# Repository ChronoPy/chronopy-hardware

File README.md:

# ChronoPy - Open Hardware, hacker freindly, wrist watch based on the OHS2020 badge
* [Hackaday.io project page](https://hackaday.io/project/168483-open-hardware-summit-2020-badge)
* [OHS 2020 website](http://2020.oshwa.org/)

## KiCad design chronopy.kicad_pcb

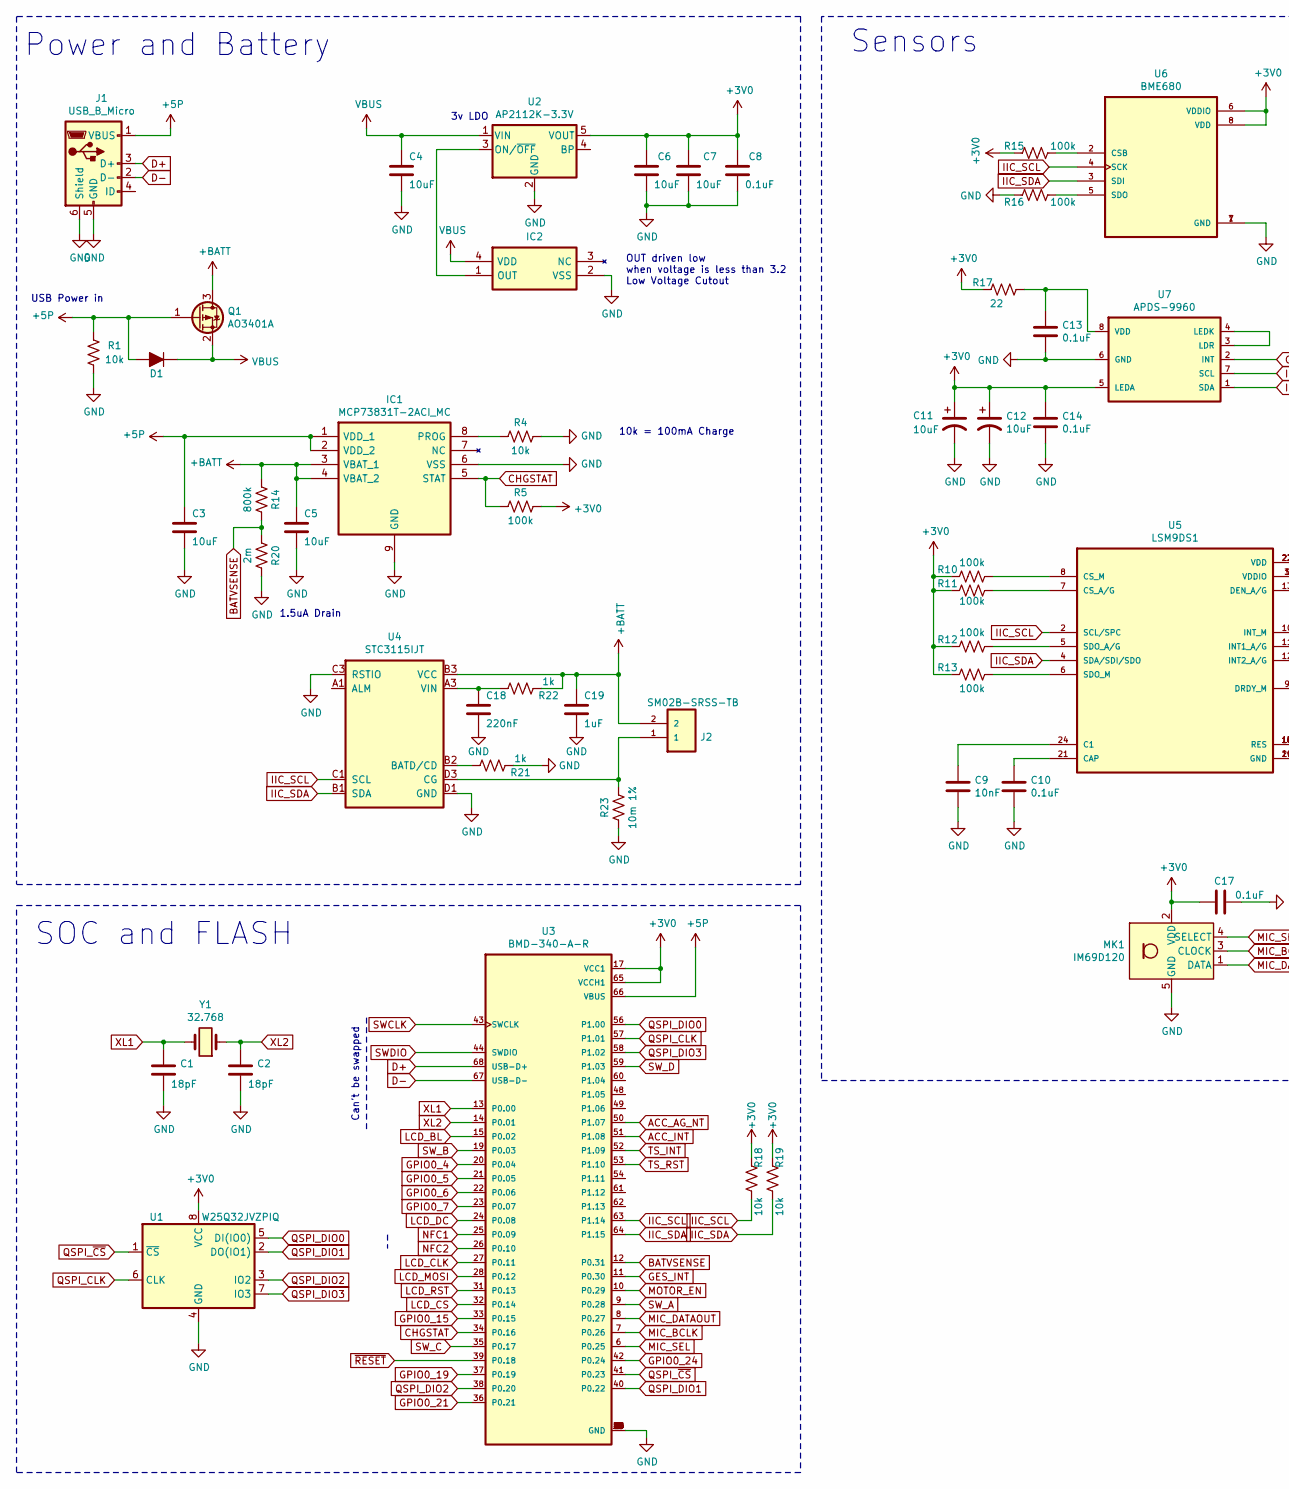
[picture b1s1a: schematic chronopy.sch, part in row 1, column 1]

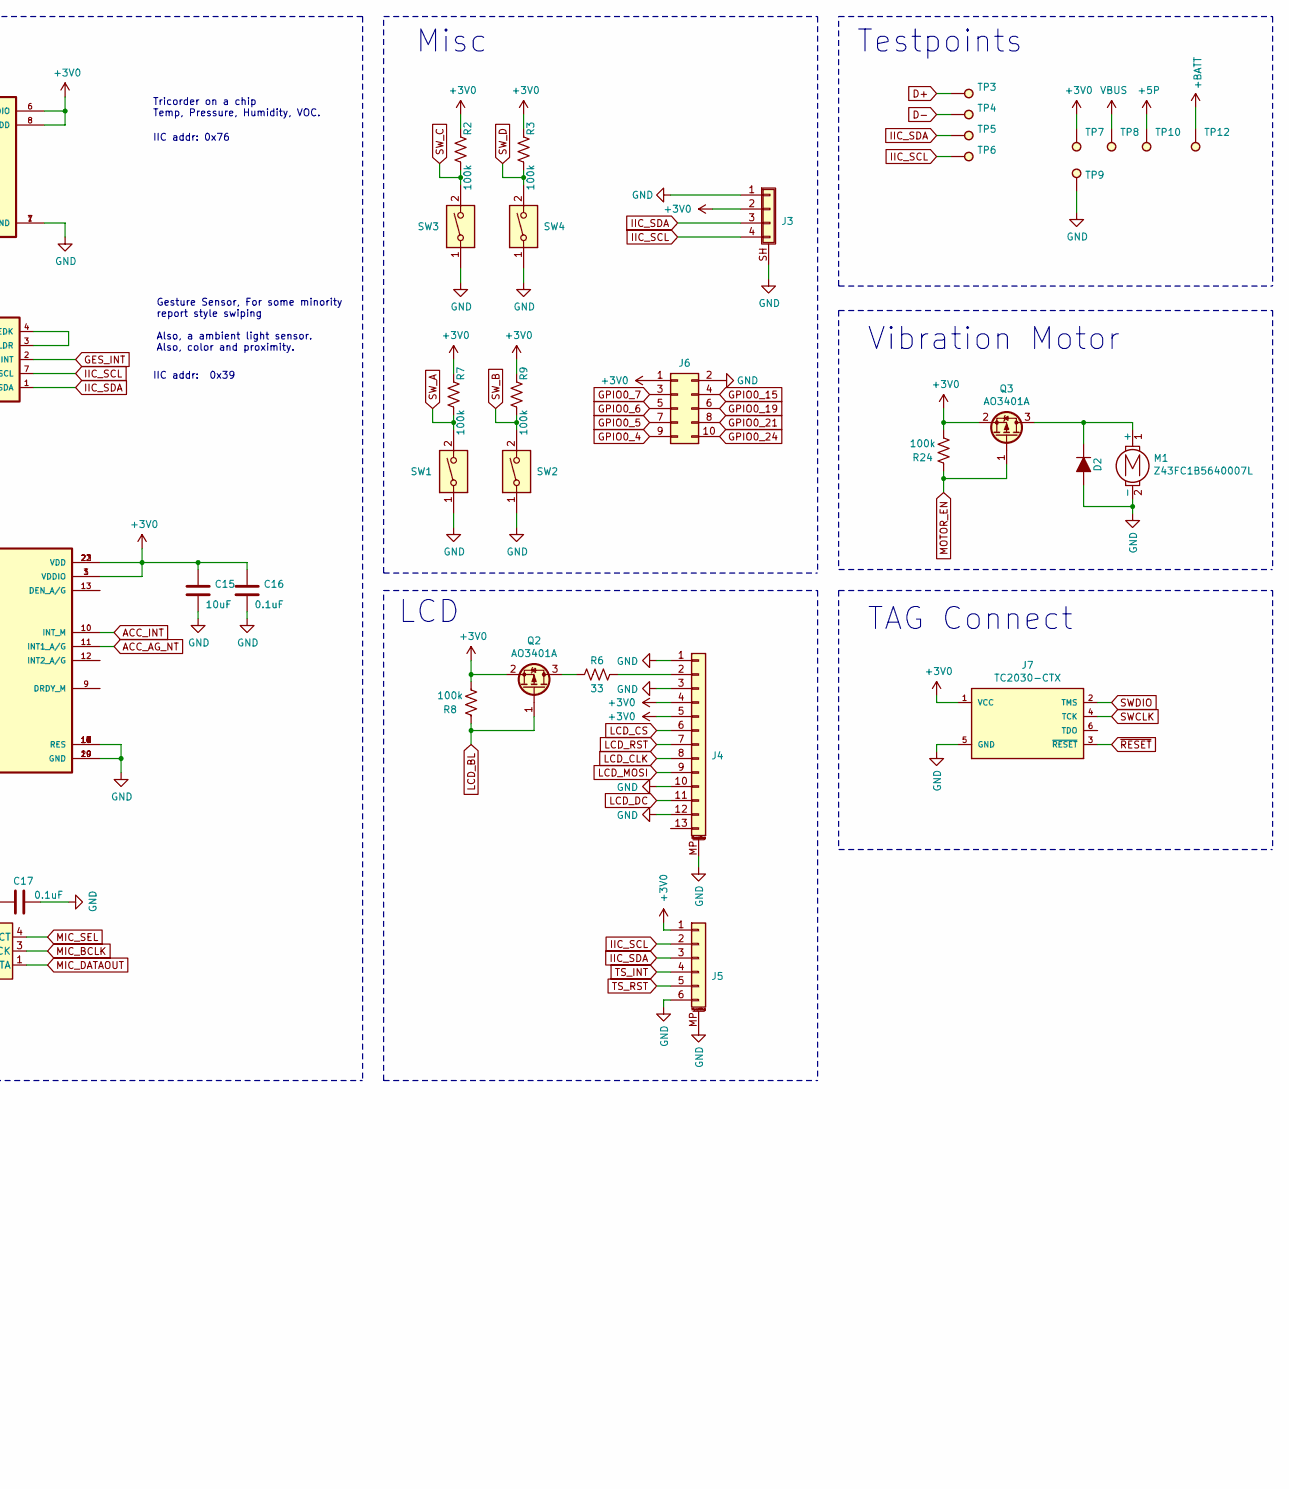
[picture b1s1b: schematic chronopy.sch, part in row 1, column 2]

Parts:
C1, C2: 18pF; C_0402
C3, C4, C5, C6, C7, C15: 10uF; C_0402
C8, C10, C13, C14, C16, C17: 0.1uF; C_0402
C9: 10nF; C_0402
C11, C12: 10uF; C_0805_2012Metric
C18: 220nF; C_0402
C19: 1uF; C_0402
D1, D2: D; D_SOD-323
IC1: MCP73831T-2ACI_MC; SON50P300X200X100-9N-D; Mouser Part Number 579-MCP73831T-2ACIMC
IC2: S-1000C32-I4T1U_S-1000C32-I4T1U; SNT-4A; Manufacturer_Part_Number S-1000C32-I4T1U; Mouser Part Number 628-S-1000C32-I4T1U
J1: USB_B_Micro; USB_Micro-B_Molex-105017-0001
J2: SM02B-SRSS-TB
J3: Conn_01x04_Shielded; JST_SM04B-SRSS-TB(LF)(SN)
J4: Conn_01x13_MountingPin; Hirose_FH26W-13S-0.3SHW_2Rows-13Pins-1MP_P0.60mm
J5: Conn_01x06_MountingPin; Hirose_FH19C-6S-0.5SH_1x06-1MP_P0.50mm
J6: Conn_02x05_Odd_Even; PinHeader_2x05_P1.27mm_Horizontal
J7: TC2030-CTX; TC2030-IDC-NL
M1: Z43FC1B5640007L
MK1: IM69D120; Infineon_PG-LLGA-5-1
Q1, Q2, Q3: AO3401A; SOT-23
R1, R4, R18, R19: 10k; R_0402
R2, R3, R5, R7, R8, R9, R10, R11, R12, R13, R15, R16, R24: 100k; R_0402
R6: 33; R_0402
R14: 800k; R_0402
R17: 22; R_0402
R20: 2m; R_0402
R21, R22: 1k; R_0402
R23: 10m 1%; R_0603_1608Metric
SW1, SW2, SW3, SW4: SW_DIP_x01; SW_TL3340AF160QG
TP3, TP4, TP5, TP6, TP7, TP8, TP9, TP10, TP12: TestPoint; Test_Point_Pad_d1.0mm
U1: W25Q32JVZPIQ; SON127P600X500X80-9N
U2: AP2112K-3.3V; SOT-23-5
U3: BMD-340-A-R; RIGADO_BMD-340-A-R
U4: STC3115IJT; CSP-10
U5: LSM9DS1; PQFN24P43_350X300X102L35X23N
U6: BME680; PSON80P300X300X100-8N
U7: APDS-9960
Y1: 32.768; Crystal_SMD_MicroCrystal_CM9V-T1A-2pin_1.6x1.0mm

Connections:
+3V0: C6.1, C7.1, C8.1, C11.1, C12.1, C14.1, C15.1, C16.1, C17.1, J3.2, J4.4, J4.5, J5.1, J6.1, J7.1 (VCC), MK1.2 (VDD), Q2.2 (S), Q3.2 (S), R2.2, R3.2, R5.1, R7.2, R8.1, R9.2, R10.2, R11.2, R12.2, R13.2, R15.2, R17.2, R18.2, R19.2, R24.1, TP7.1, U1.8 (VCC), U2.5 (VOUT), U3.17 (VCC1), U3.65 (VCCH1), U5.1 (VDDIO), U5.3 (VDDIO), U5.22 (VDD), U5.23 (VDD), U6.6 (VDDIO), U6.8 (VDD), U7.5 (LEDA)
+5P: C3.1, D1.2 (A), IC1.1 (VDD_1), IC1.2 (VDD_2), J1.1 (VBUS), Q1.1 (G), R1.2, TP10.1, U3.66 (VBUS)
+BATT: C5.1, C19.1, IC1.3 (VBAT_1), IC1.4 (VBAT_2), J2.2, Q1.3 (D), R14.2, R22.2, TP12.1, U4.B3 (VCC)
ACC_AG_NT: U3.50 (P1.07), U5.11 (INT1_A/G)
ACC_INT: U3.51 (P1.08), U5.10 (INT_M)
BATVSENSE: R14.1, R20.2, U3.12 (P0.31)
CHGSTAT: IC1.5 (STAT), R5.2, U3.34 (P0.16)
D+: J1.3 (D+), TP3.1, U3.68 (USB-D+)
D-: J1.2 (D-), TP4.1, U3.67 (USB-D-)
GES_INT: U3.11 (P0.30), U7.2 (INT)
GND: C1.2, C2.2, C3.2, C4.2, C5.2, C6.2, C7.2, C8.2, C9.1, C10.1, C11.2, C12.2, C13.2, C14.2, C15.2, C16.2, C17.2, C18.2, C19.2, D2.2 (A), IC1.6 (VSS), IC1.9 (GND), IC2.2 (VSS), J1.5 (GND), J1.6 (Shield), J3.1, J3.SH (Shield), J4.1, J4.3, J4.10, J4.12, J4.MP (MountPin), J5.6, J5.MP (MountPin), J6.2, J7.5 (GND), M1.2 (-), MK1.5 (GND), R1.1, R4.1, R16.2, R20.1, R21.2, R23.1, SW1.1, SW2.1, SW3.1, SW4.1, TP9.1, U1.4 (GND), U2.2 (GND), U3.1 (GND), U3.2 (GND), U3.3 (GND), U3.4 (GND), U3.5 (GND), U3.16 (GND), U3.18 (GND), U3.29 (GND), U3.30 (GND), U3.45 (GND), U3.46 (GND), U3.47 (GND), U3.55 (GND), U4.C3 (RSTIO), U4.D1 (GND), U5.14 (RES), U5.15 (RES), U5.16 (RES), U5.17 (RES), U5.18 (RES), U5.19 (GND), U5.20 (GND), U6.1 (GND), U6.7 (GND), U7.6 (GND)
GPIO0_4: J6.9, U3.20 (P0.04)
GPIO0_5: J6.7, U3.21 (P0.05)
GPIO0_6: J6.5, U3.22 (P0.06)
GPIO0_7: J6.3, U3.23 (P0.07)
GPIO0_15: J6.4, U3.33 (P0.15)
GPIO0_19: J6.6, U3.37 (P0.19)
GPIO0_21: J6.8, U3.36 (P0.21)
GPIO0_24: J6.10, U3.42 (P0.24)
IIC_SCL: J3.4, J5.2, R18.1, TP6.1, U3.63 (P1.14), U4.C1 (SCL), U5.2 (SCL/SPC), U6.4 (SCK), U7.7 (SCL)
IIC_SDA: J3.3, J5.3, R19.1, TP5.1, U3.64 (P1.15), U4.B1 (SDA), U5.4 (SDA/SDI/SDO), U6.3 (SDI), U7.1 (SDA)
LCD_BL: Q2.1 (G), R8.2, U3.15 (P0.02)
LCD_CLK: J4.8, U3.27 (P0.11)
LCD_CS: J4.6, U3.32 (P0.14)
LCD_DC: J4.11, U3.24 (P0.08)
LCD_MOSI: J4.9, U3.28 (P0.12)
LCD_RST: J4.7, U3.31 (P0.13)
MIC_BCLK: MK1.3 (CLOCK), U3.7 (P0.26)
MIC_DATAOUT: MK1.1 (DATA), U3.8 (P0.27)
MIC_SEL: MK1.4 (SELECT), U3.6 (P0.25)
MOTOR_EN: Q3.1 (G), R24.2, U3.10 (P0.29)
NFC1: U3.25 (P0.09)
NFC2: U3.26 (P0.10)
unnamed: C9.2, U5.24 (C1)
unnamed: C10.2, U5.21 (CAP)
unnamed: C13.1, R17.1, U7.8 (VDD)
unnamed: C18.1, R22.1, U4.A3 (VIN)
unnamed: D2.1 (K), M1.1 (+), Q3.3 (D)
unnamed: IC1.8 (PROG), R4.2
unnamed: IC2.1 (OUT), U2.3 (ON/~OFF~)
unnamed: J2.1, R23.2, U4.D3 (CG)
unnamed: J4.2, R6.1
unnamed: Q2.3 (D), R6.2
unnamed: R10.1, U5.8 (CS_M)
unnamed: R11.1, U5.7 (CS_A/G)
unnamed: R12.1, U5.5 (SDO_A/G)
unnamed: R13.1, U5.6 (SDO_M)
unnamed: R15.1, U6.2 (CSB)
unnamed: R16.1, U6.5 (SDO)
unnamed: R21.1, U4.B2 (BATD/CD)
unnamed: U7.3 (LDR), U7.4 (LEDK)
QSPI_CLK: U1.6 (CLK), U3.57 (P1.01)
QSPI_DIO0: U1.5 (DI(IO0)), U3.56 (P1.00)
QSPI_DIO1: U1.2 (DO(IO1)), U3.40 (P0.22)
QSPI_DIO2: U1.3 (IO2), U3.38 (P0.20)
QSPI_DIO3: U1.7 (IO3), U3.58 (P1.02)
QSPI_~CS: U1.1 (~CS), U3.41 (P0.23)
SWCLK: J7.4 (TCK), U3.43 (SWCLK)
SWDIO: J7.2 (TMS), U3.44 (SWDIO)
SW_A: R7.1, SW1.2, U3.9 (P0.28)
SW_B: R9.1, SW2.2, U3.19 (P0.03)
SW_C: R2.1, SW3.2, U3.35 (P0.17)
SW_D: R3.1, SW4.2, U3.59 (P1.03)
TS_INT: J5.4, U3.52 (P1.09)
TS_RST: J5.5, U3.53 (P1.10)
VBUS: C4.1, D1.1 (K), IC2.4 (VDD), Q1.2 (S), TP8.1, U2.1 (VIN)
XL1: C1.1, U3.13 (P0.00), Y1.2
XL2: C2.1, U3.14 (P0.01), Y1.1
~RESET: J7.3 (~RESET), U3.39 (P0.18)

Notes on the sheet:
3v LDO
OUT driven low when voltage is less than 3.2 Low Voltage Cutout
USB Power in
10k = 100mA Charge
Power and Battery
LCD
SOC and FLASH
Sensors
Can't be swapped
Testpoints
Gesture Sensor, For some minority report style swiping Also, a ambient light sensor. Also, color and proximity.
Tricorder on a chip Temp, Pressure, Humidity, VOC.
IIC addr: 0x76
IIC addr: 0x39
1.5uA Drain
Misc
Vibration Motor
TAG Connect

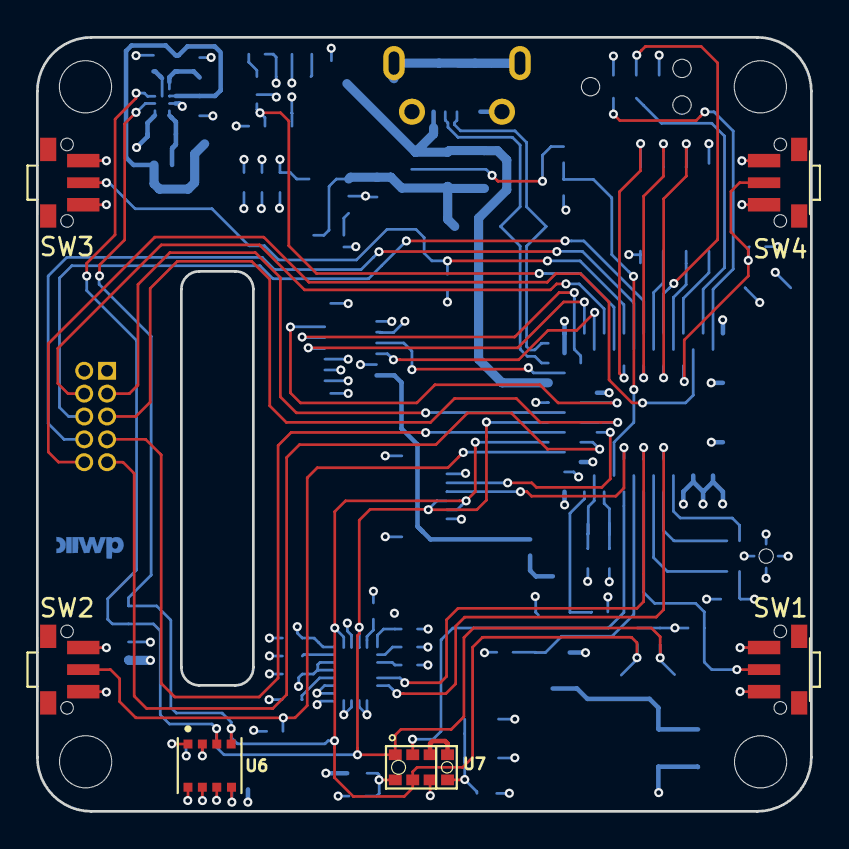
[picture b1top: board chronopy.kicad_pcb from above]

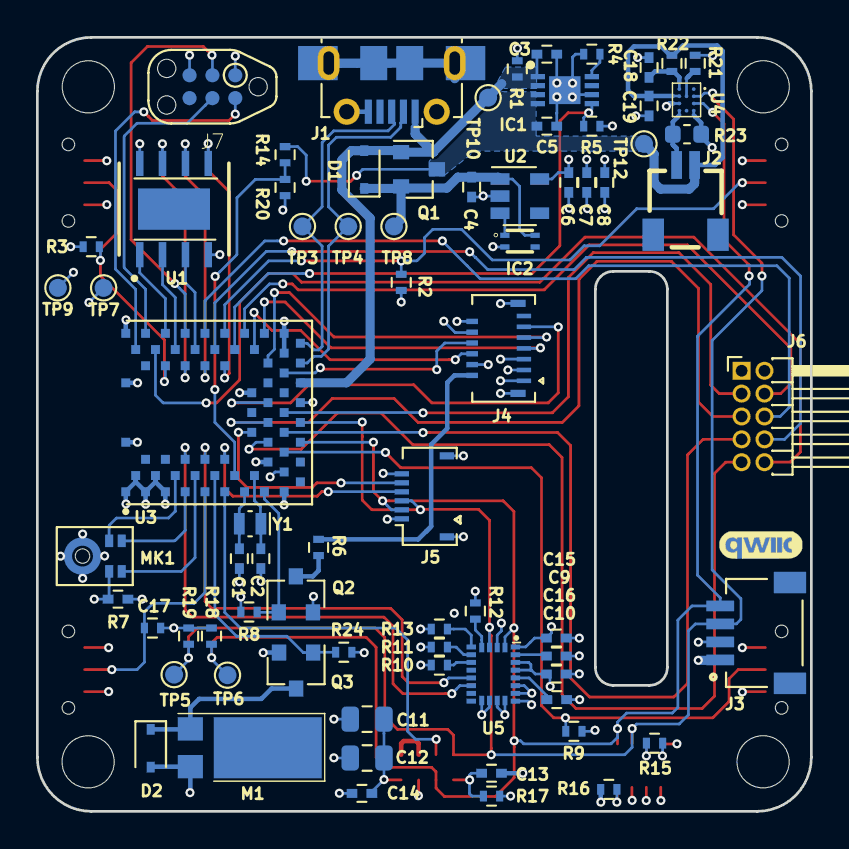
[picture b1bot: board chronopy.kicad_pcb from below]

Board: 4 copper layers, 43.0 x 43.0 mm, 81 parts (75 on the bottom side), 67 nets.

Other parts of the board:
Ref**: Val**; Qwiic lozenge curves-shenzen

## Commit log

2020-08-18 Update README a bit
2020-09-11 Rename everything to ChronoPY and clean up a bit
2020-09-11 Sync plots in new directory
2020-09-11 Remove stale Gerbers
2020-09-11 Rename fab files
2020-09-11 Remove stale schematic pdf
2020-09-11 Rename renders to chronopy
2020-09-11 Move various assets into a separate directory
2020-09-11 Add datasheets for new 1.3" SPI LCD and connectors
2020-09-11 Add vendor step model for the new LCD
2020-09-11 Tidy up schematic and add TODO list
2020-09-11 Remove old renders from assets
2020-09-11 Remove stale step model from assets
2020-09-11 Remove deleted library for lib table
2020-09-11 Update footprint references in schematic and sync
2020-09-11 Update hole size of mic in library and PCB
2020-09-21 Some updates from the weekend
2020-09-27 Adding STC3117IJT
2020-09-28 Added Fuel Gauge IC
2020-10-31 Clean up schematic changes for fuel gauge
    Cleans schematic a bit and start the layout for the fuel gauge.
2020-12-04 Adds new fuel gauge and vibration motor
2020-12-06 Switch to side shooter buttons and add Tag connect
2020-12-06 Tweak fuel gauge routing a bit
2020-12-10 Generate outputs for fab
